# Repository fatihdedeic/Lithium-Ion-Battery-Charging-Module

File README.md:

# Lithium-Ion-Battery-Charging-Module
500mA Lithium Ion battery linear charging module capable of charging up to 4.7v.

TP4057 IC provides following features:
-  Reverse polarity application protection
-  Constant charging current/voltage regulation
-  Charge status indicators
-  Preset charge voltage within 1% accuracy
-  C/10 Charge termination

INPUT VALUES
-  Voltage: 4v to 9v
-  Current: 0mA to 500mA

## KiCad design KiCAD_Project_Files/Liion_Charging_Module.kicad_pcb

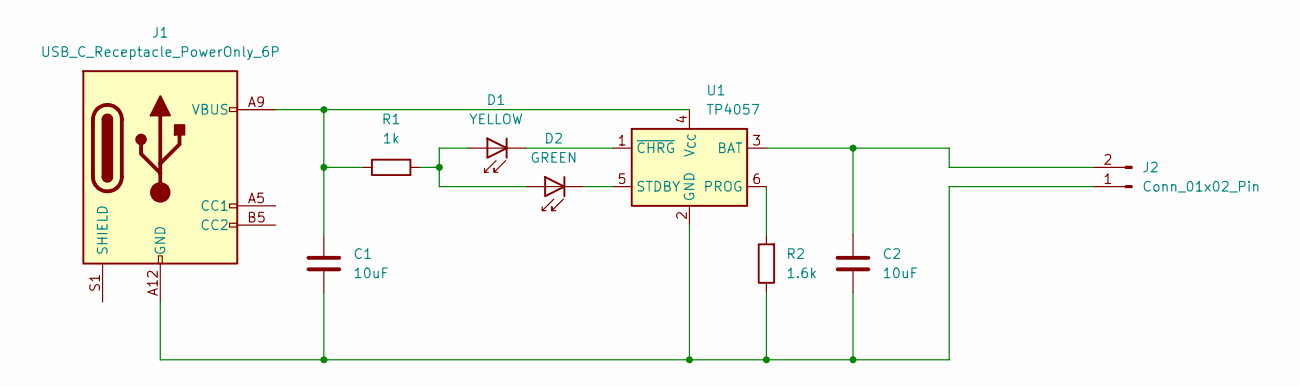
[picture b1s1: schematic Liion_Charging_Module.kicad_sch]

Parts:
C1, C2: 10uF; C_0805_2012Metric_Pad1.18x1.45mm_HandSolder
D1: YELLOW; LED_D5.0mm_IRGrey
D2: GREEN; LED_D5.0mm_IRGrey
J1: USB_C_Receptacle_PowerOnly_6P; USB_C_Receptacle_GCT_USB4125-xx-x_6P_TopMnt_Horizontal
J2: Conn_01x02_Pin; JST_PH_S2B-PH-K_1x02_P2.00mm_Horizontal
R1: 1k; R_0805_2012Metric_Pad1.20x1.40mm_HandSolder
R2: 1.6k; R_0805_2012Metric_Pad1.20x1.40mm_HandSolder
U1: TP4057; TSOT-23-6_HandSoldering

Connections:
unnamed: D1.2 (A), D2.2 (A), R1.2
unnamed: D1.1 (K), U1.1 (~CHRG)
unnamed: D2.1 (K), U1.5 (STDBY)
unnamed: C1.2, C2.2, J1.A12 (GND), J1.B12 (GND), J2.1, R2.1, U1.2 (GND)
unnamed: C2.1, J2.2, U1.3 (BAT)
unnamed: R2.2, U1.6 (PROG)
unnamed: C1.1, J1.A9 (VBUS), J1.B9 (VBUS), R1.1, U1.4 (V_{CC})

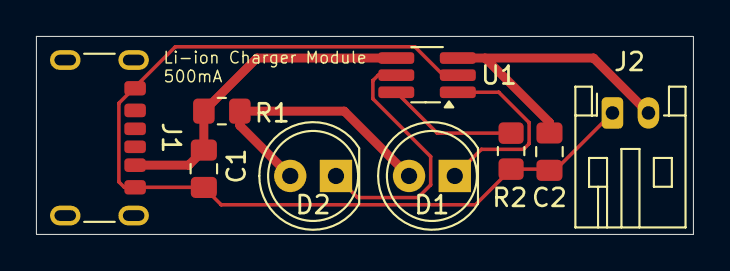
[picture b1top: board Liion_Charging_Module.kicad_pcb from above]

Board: 2 copper layers, 36.5 x 11.0 mm, 9 parts (0 on the bottom side), 7 nets.

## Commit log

2025-03-14 Created 3D render folder
2025-03-14 Created Design Docs folder
2025-03-14 Create KiCAD design docs folder
2025-03-14 Uploaded 3D renders
2025-03-14 Added project files
